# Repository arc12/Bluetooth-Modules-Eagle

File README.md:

# Bluetooth Modules Eagle CAD Files
"Breakout" boards designed for HM10 and HM11 Bluetooth (BT) modules and pin-equivalent clones (etc) based on TI CC2540/2541 SoC.

These are intended to be usable for both breadboard prototyping and as modules for "finished" items (although admittedly in a DIY concept). Unlike breakouts on the open market, it is strictly a 3.3V approach. Both modules have a 5-pin header exposing the "debug" interface pins of the CC254x which can be used for loading new firmware (see notes below) and probably for actual debugging operations with a suitable IDE. The 5-pin header is semi-detached from the rest of the board due to a milled slot so that it can be cut off if not required (but pay attention to making sure the cut copper tracks don't have short-cuts.

As a "finished" item, the concept for the two boards differs:
- For the HM11 based board, the main header is arranged such that the central 6 pins match the pinout of popular USB-Serial boards based on CH340. The intention is that the BT board is plugged into the same header as is used for loading the firmware and is used to provide wireless serial output from a separate MCU and its associated sensors, or to provide serial input for control etc. Notice that there is a cuttable (and re-solderable) link adjacent to the header pins where the CH340 has DTR and RTS/CTS pins. Cut these if these are being used for bootloader control.
- For the HM10 based board, the scenario in mind is that the CC254x is used without a controlling MCU, with its I/O pins being used for various sensors or output connected to the main header.

Each board has one resistor and one capacitor as 1206 size SMD pads. These are optional; the capacitor is good practice for power supply and the resistor is intended for the "finished" scenarios.

## Changing Firmware
This is relevant to "clone" modules, although it may not work on all clones (definitely not if the CC254x is not genuine).

There are two fairly easy approaches:
- Using an ESP8266. See: https://github.com/Jason2866/CCLoader
- Using a Raspberry Pi. See: https://github.com/exotulip/CC2541-programmer

There are a lot of people who have essentially re-hashed the ESP8266 instructions and published online and the arduino forum is full of various accounts of success or failure. Using the boards presented here, with 3.3V native devices such as the RPi and ESP8266 should make life easier.

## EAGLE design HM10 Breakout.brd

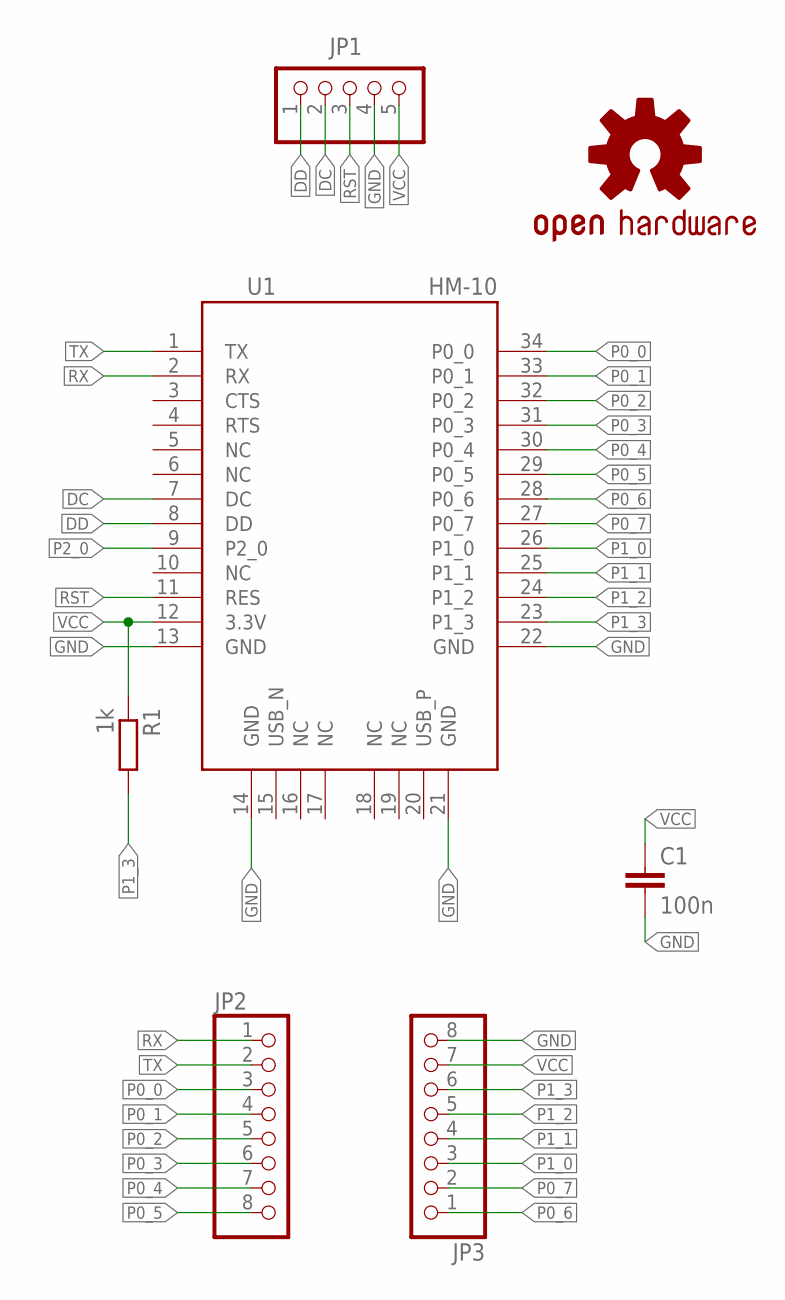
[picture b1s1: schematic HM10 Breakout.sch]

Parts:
C1: 100n; 1206
JP1: PINHD-1X5; 1X05
JP2, JP3: PINHD-1X8; 1X08
LOGO1: OSHW-LOGOM; OSHW-LOGO-M
R1: 1k; R1206
U1: HM-10

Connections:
DC: JP1.2, U1.7 (DC)
DD: JP1.1, U1.8 (DD)
GND: C1.2, JP1.4, JP3.8, U1.13 (GND), U1.14 (GND), U1.21 (GND), U1.22 (GND)
P0_0: JP2.3, U1.34 (P0_0)
P0_1: JP2.4, U1.33 (P0_1)
P0_2: JP2.5, U1.32 (P0_2)
P0_3: JP2.6, U1.31 (P0_3)
P0_4: JP2.7, U1.30 (P0_4)
P0_5: JP2.8, U1.29 (P0_5)
P0_6: JP3.1, U1.28 (P0_6)
P0_7: JP3.2, U1.27 (P0_7)
P1_0: JP3.3, U1.26 (P1_0)
P1_1: JP3.4, U1.25 (P1_1)
P1_2: JP3.5, U1.24 (P1_2)
P1_3: JP3.6, R1.2, U1.23 (P1_3)
P2_0: U1.9 (P2_0)
RST: JP1.3, U1.11 (RES)
RX: JP2.1, U1.2 (RX)
TX: JP2.2, U1.1 (TX)
VCC: C1.1, JP1.5, JP3.7, R1.1, U1.12 (3.3V)

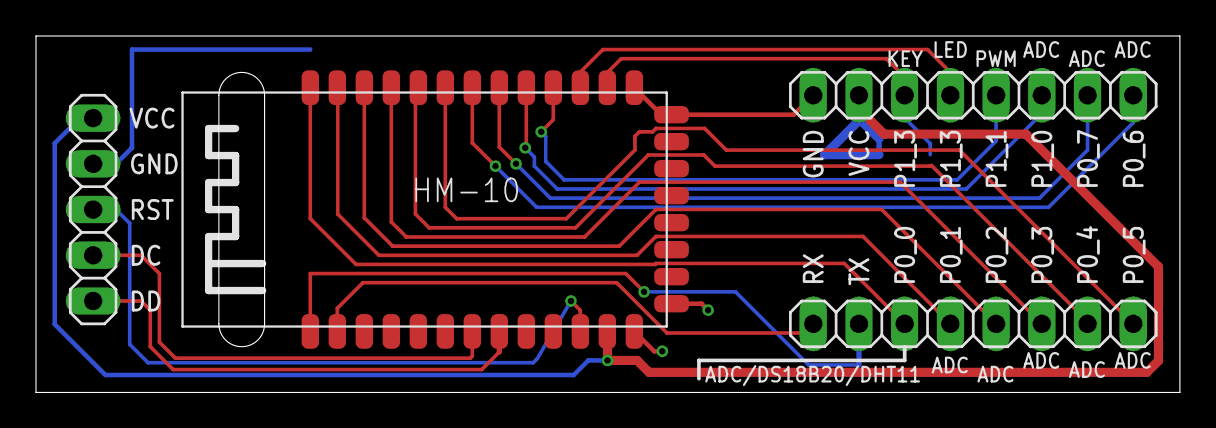
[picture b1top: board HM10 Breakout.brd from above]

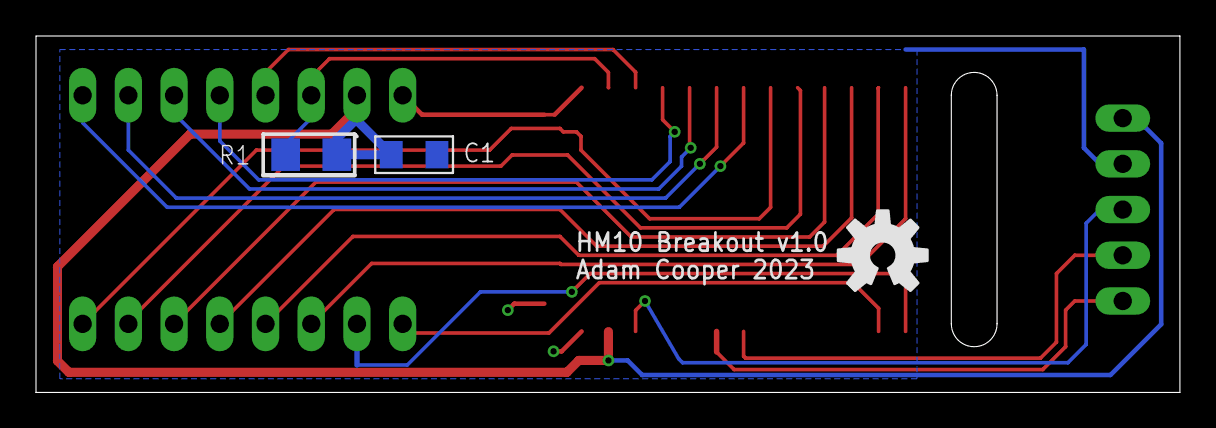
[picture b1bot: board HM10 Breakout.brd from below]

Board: 2 copper layers, 63.6 x 19.8 mm, 7 parts (3 on the bottom side), 19 nets.

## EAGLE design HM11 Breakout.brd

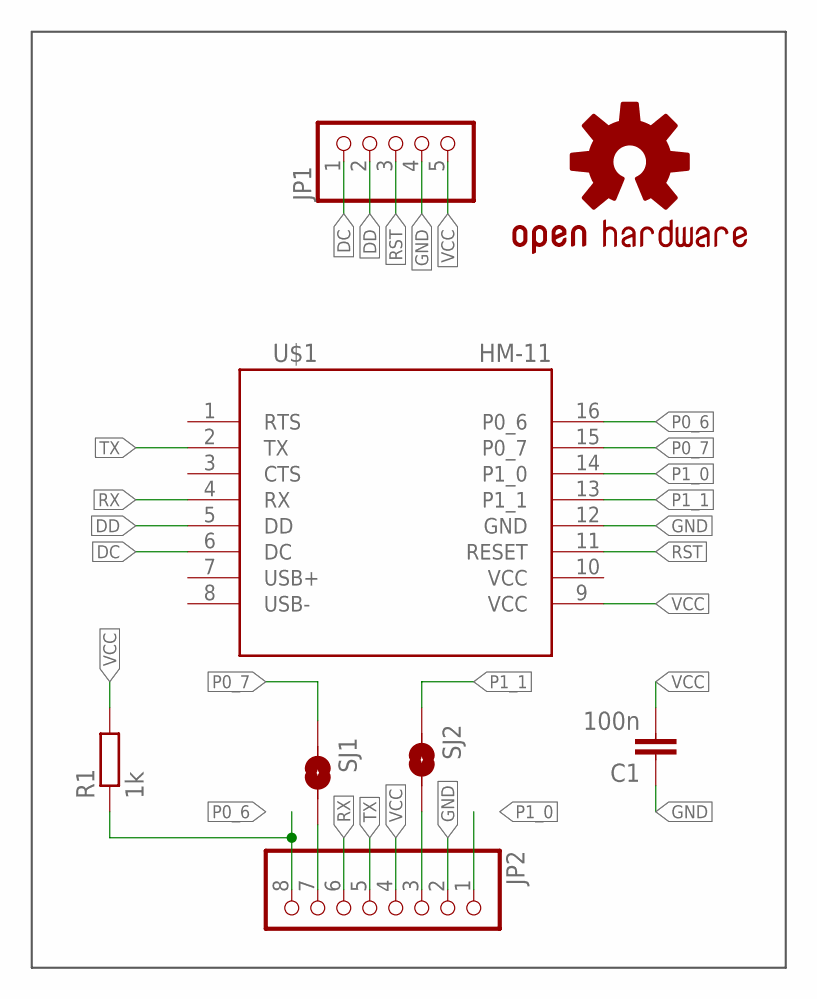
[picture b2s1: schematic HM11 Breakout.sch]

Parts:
C1: 100n; 1206
JP1: PINHD-1X5; 1X05
JP2: PINHD-1X8; 1X08
LOGO1: OSHW-LOGOM; OSHW-LOGO-M
R1: 1k; R1206
SJ1, SJ2: SOLDERJUMPERTRACE; SJ_2S-TRACE
U$1: HM-11

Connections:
DC: JP1.1, U$1.6 (DC)
DD: JP1.2, U$1.5 (DD)
GND: C1.1, JP1.4, JP2.2, U$1.12 (GND)
unnamed: JP2.7, SJ1.1
unnamed: JP2.3, SJ2.1
P0_6: JP2.8, R1.1, U$1.16 (P0_6)
P0_7: SJ1.2, U$1.15 (P0_7)
P1_0: JP2.1, U$1.14 (P1_0)
P1_1: SJ2.2, U$1.13 (P1_1)
RST: JP1.3, U$1.11 (RESET)
RX: JP2.6, U$1.4 (RX)
TX: JP2.5, U$1.2 (TX)
VCC: C1.2, JP1.5, JP2.4, R1.2, U$1.9 (VCC)

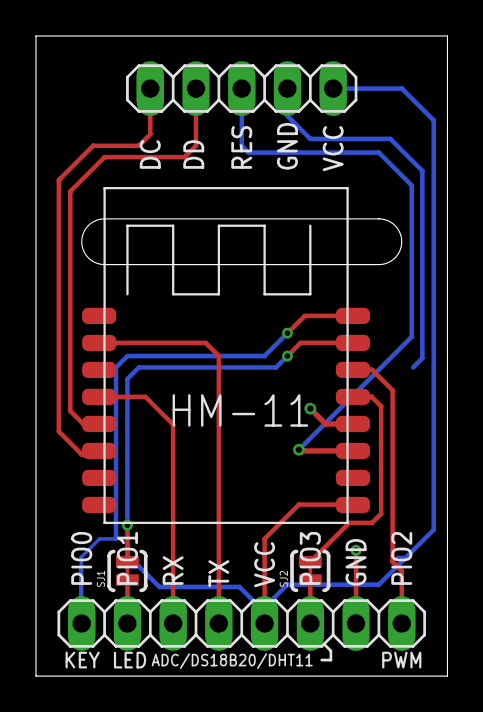
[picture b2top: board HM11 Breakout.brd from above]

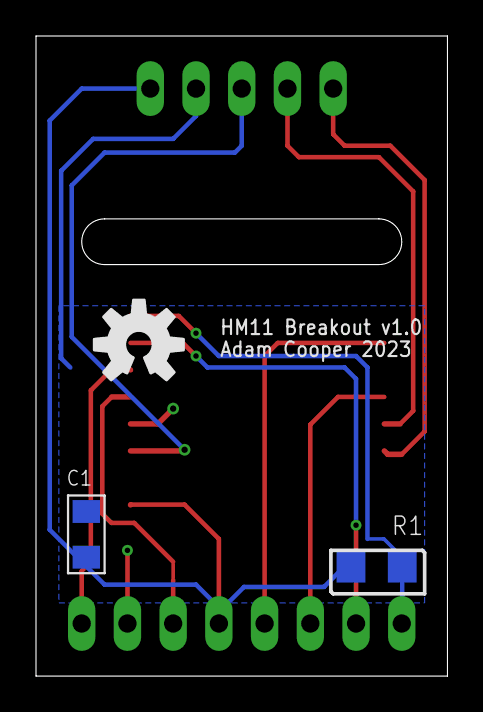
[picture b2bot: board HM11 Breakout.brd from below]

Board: 2 copper layers, 22.9 x 35.6 mm, 8 parts (3 on the bottom side), 13 nets.

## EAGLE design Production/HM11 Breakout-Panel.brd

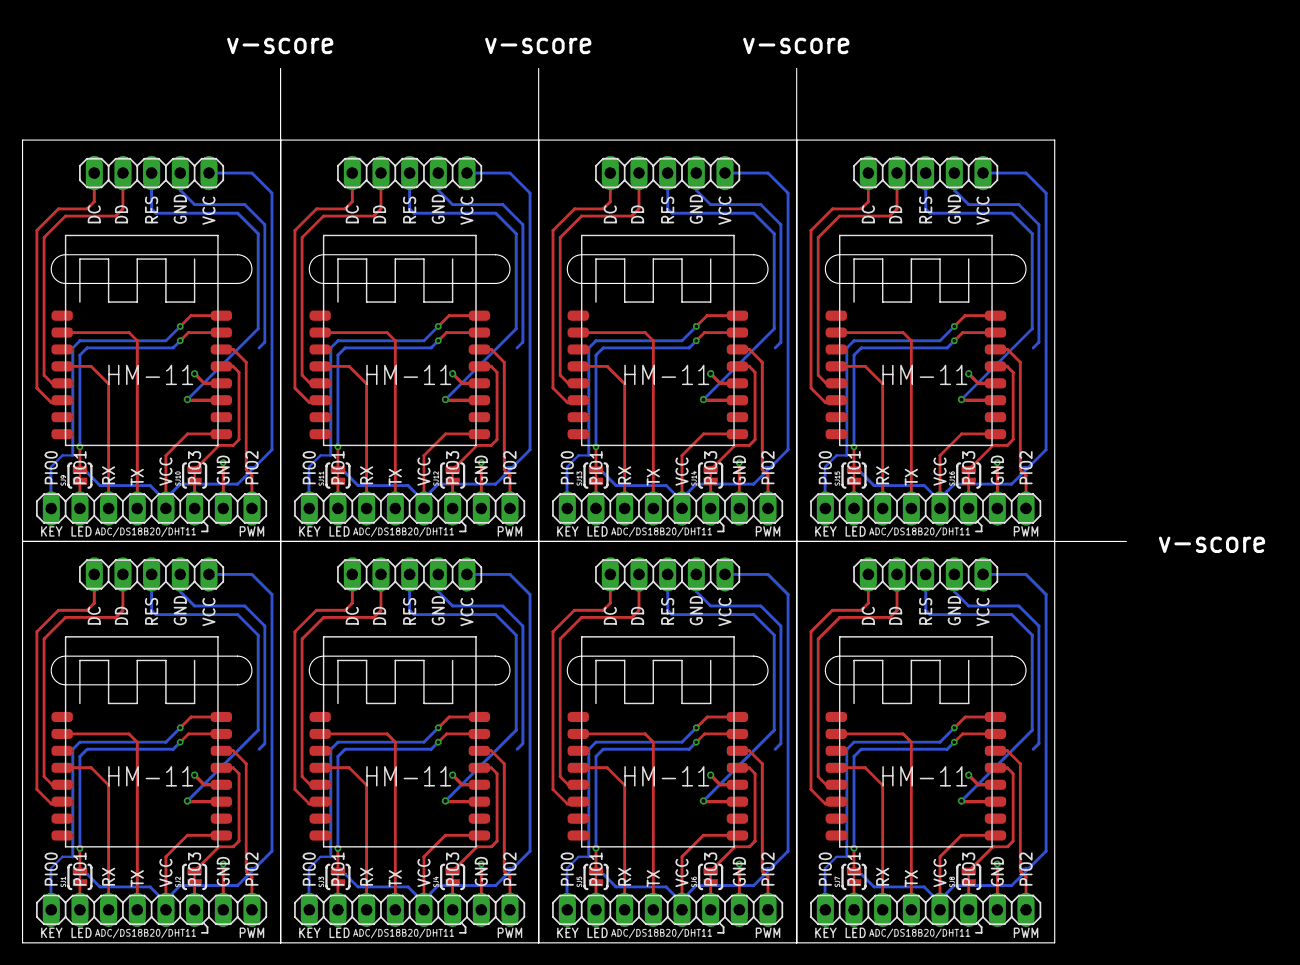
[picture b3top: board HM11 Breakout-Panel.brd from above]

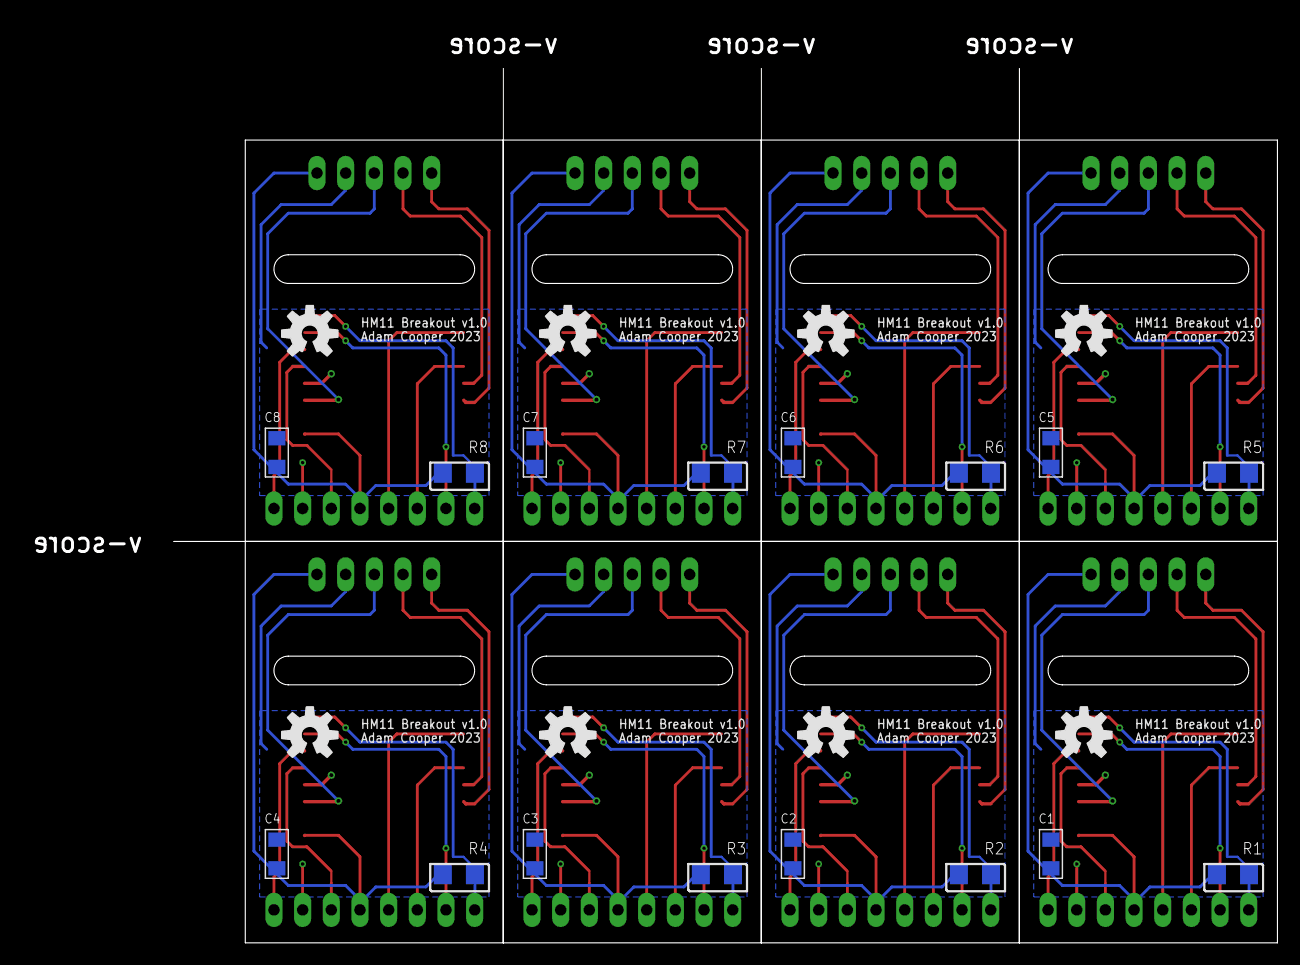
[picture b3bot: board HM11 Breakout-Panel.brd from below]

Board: 2 copper layers, 111.2 x 81.5 mm, 64 parts (24 on the bottom side), 104 nets.

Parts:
C1, C2, C3, C4, C5, C6, C7, C8: 100n; 1206
JP1, JP3, JP5, JP7, JP9, JP11, JP13, JP15: 1X05
JP2, JP4, JP6, JP8, JP10, JP12, JP14, JP16: 1X08
LOGO1, LOGO2, LOGO3, LOGO4, LOGO5, LOGO6, LOGO7, LOGO8: OSHW-LOGOM; OSHW-LOGO-M
R1, R2, R3, R4, R5, R6, R7, R8: 1k; R1206
SJ1, SJ2, SJ3, SJ4, SJ5, SJ6, SJ7, SJ8, SJ9, SJ10, SJ11, SJ12, SJ13, SJ14, SJ15, SJ16: SOLDERJUMPERTRACE; SJ_2S-TRACE
U$1, U$2, U$3, U$4, U$5, U$6, U$7, U$8: HM-11

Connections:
DC: JP1.1, U$1.6
DC1: JP3.1, U$2.6
DC2: JP5.1, U$3.6
DC3: JP7.1, U$4.6
DC4: JP9.1, U$5.6
DC5: JP11.1, U$6.6
DC6: JP13.1, U$7.6
DC7: JP15.1, U$8.6
DD: JP1.2, U$1.5
DD1: JP3.2, U$2.5
DD2: JP5.2, U$3.5
DD3: JP7.2, U$4.5
DD4: JP9.2, U$5.5
DD5: JP11.2, U$6.5
DD6: JP13.2, U$7.5
DD7: JP15.2, U$8.5
GND: C1.1, JP1.4, JP2.2, U$1.12
GND1: C2.1, JP3.4, JP4.2, U$2.12
GND2: C3.1, JP5.4, JP6.2, U$3.12
GND3: C4.1, JP7.4, JP8.2, U$4.12
GND4: C5.1, JP9.4, JP10.2, U$5.12
GND5: C6.1, JP11.4, JP12.2, U$6.12
GND6: C7.1, JP13.4, JP14.2, U$7.12
GND7: C8.1, JP15.4, JP16.2, U$8.12
unnamed: JP2.7, SJ1.1
unnamed: JP4.7, SJ3.1
unnamed: JP4.3, SJ4.1
unnamed: JP6.7, SJ5.1
unnamed: JP6.3, SJ6.1
unnamed: JP2.3, SJ2.1
unnamed: JP8.7, SJ7.1
unnamed: JP8.3, SJ8.1
unnamed: JP10.7, SJ9.1
unnamed: JP10.3, SJ10.1
unnamed: JP12.7, SJ11.1
unnamed: JP12.3, SJ12.1
unnamed: JP14.7, SJ13.1
unnamed: JP14.3, SJ14.1
unnamed: JP16.7, SJ15.1
unnamed: JP16.3, SJ16.1
P0_1: JP4.8, R2.1, U$2.16
P0_2: SJ3.2, U$2.15
P0_3: JP6.8, R3.1, U$3.16
P0_4: SJ5.2, U$3.15
P0_5: JP8.8, R4.1, U$4.16
P0_6: JP2.8, R1.1, U$1.16
P0_7: SJ1.2, U$1.15
P0_8: SJ7.2, U$4.15
P0_9: JP10.8, R5.1, U$5.16
P0_10: SJ9.2, U$5.15
P0_11: JP12.8, R6.1, U$6.16
P0_12: SJ11.2, U$6.15
P0_13: JP14.8, R7.1, U$7.16
P0_14: SJ13.2, U$7.15
P0_15: JP16.8, R8.1, U$8.16
P0_16: SJ15.2, U$8.15
P1_0: JP2.1, U$1.14
P1_1: SJ2.2, U$1.13
P1_2: JP4.1, U$2.14
P1_3: SJ4.2, U$2.13
P1_4: JP6.1, U$3.14
P1_5: SJ6.2, U$3.13
P1_6: JP8.1, U$4.14
P1_7: SJ8.2, U$4.13
P1_8: JP10.1, U$5.14
P1_9: SJ10.2, U$5.13
P1_10: JP12.1, U$6.14
P1_11: SJ12.2, U$6.13
P1_12: JP14.1, U$7.14
P1_13: SJ14.2, U$7.13
P1_14: JP16.1, U$8.14
P1_15: SJ16.2, U$8.13
RST: JP1.3, U$1.11
RST1: JP3.3, U$2.11
RST2: JP5.3, U$3.11
RST3: JP7.3, U$4.11
RST4: JP9.3, U$5.11
RST5: JP11.3, U$6.11
RST6: JP13.3, U$7.11
RST7: JP15.3, U$8.11
RX: JP2.6, U$1.4
RX1: JP4.6, U$2.4
RX2: JP6.6, U$3.4
RX3: JP8.6, U$4.4
RX4: JP10.6, U$5.4
RX5: JP12.6, U$6.4
RX6: JP14.6, U$7.4
RX7: JP16.6, U$8.4
TX: JP2.5, U$1.2
TX1: JP4.5, U$2.2
TX2: JP6.5, U$3.2
TX3: JP8.5, U$4.2
TX4: JP10.5, U$5.2
TX5: JP12.5, U$6.2
TX6: JP14.5, U$7.2
TX7: JP16.5, U$8.2
VCC: C1.2, JP1.5, JP2.4, R1.2, U$1.9
VCC1: C2.2, JP3.5, JP4.4, R2.2, U$2.9
VCC2: C3.2, JP5.5, JP6.4, R3.2, U$3.9
VCC3: C4.2, JP7.5, JP8.4, R4.2, U$4.9
VCC4: C5.2, JP9.5, JP10.4, R5.2, U$5.9
VCC5: C6.2, JP11.5, JP12.4, R6.2, U$6.9
VCC6: C7.2, JP13.5, JP14.4, R7.2, U$7.9
VCC7: C8.2, JP15.5, JP16.4, R8.2, U$8.9

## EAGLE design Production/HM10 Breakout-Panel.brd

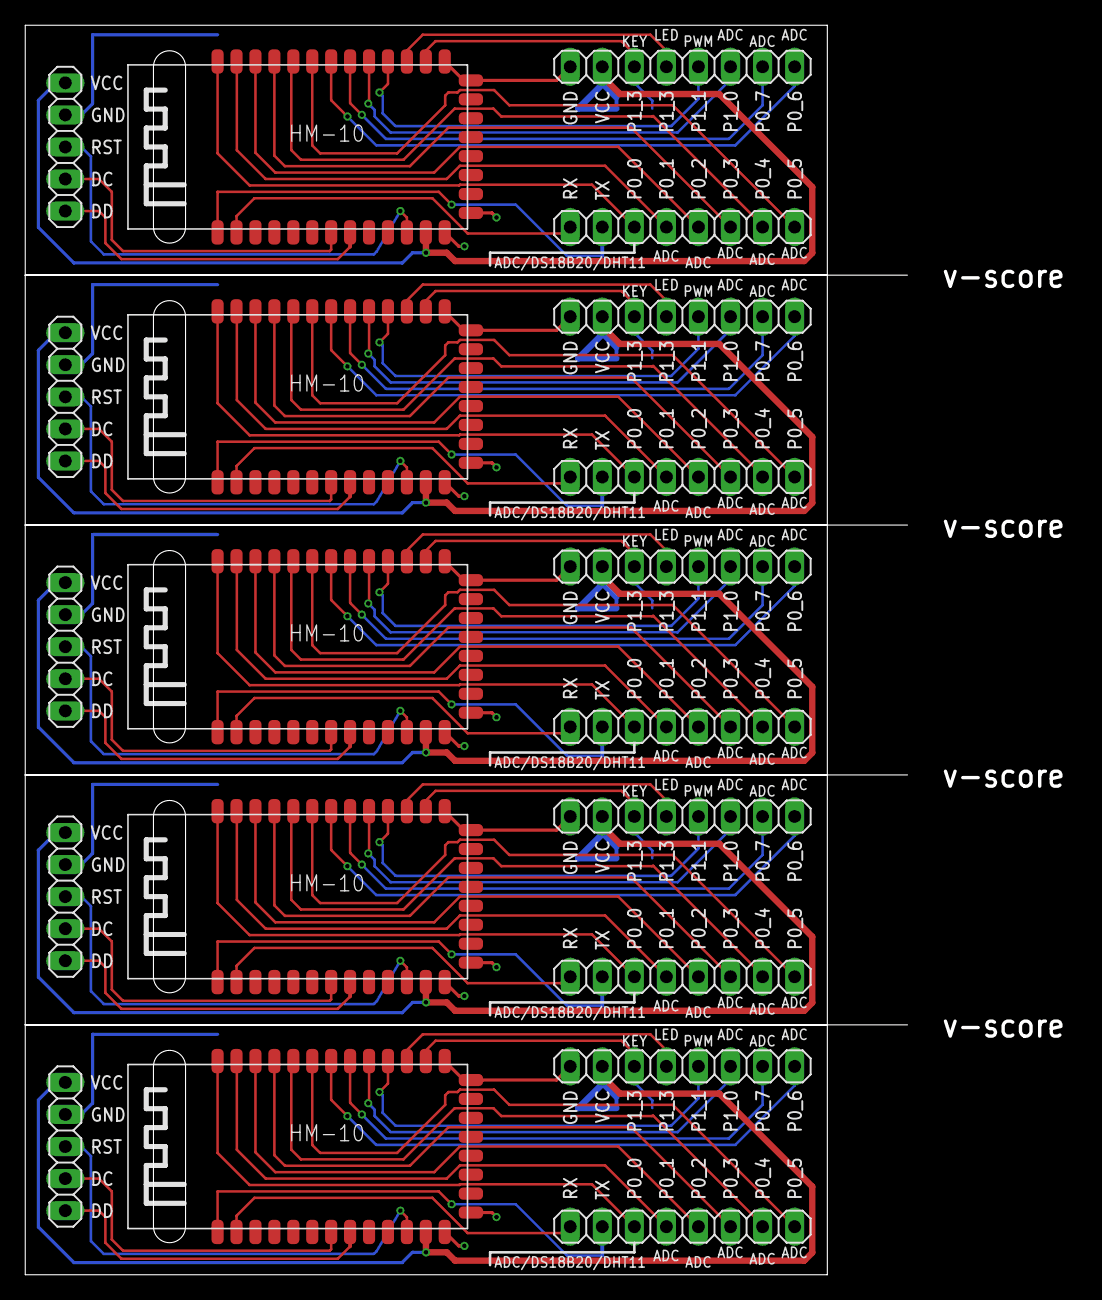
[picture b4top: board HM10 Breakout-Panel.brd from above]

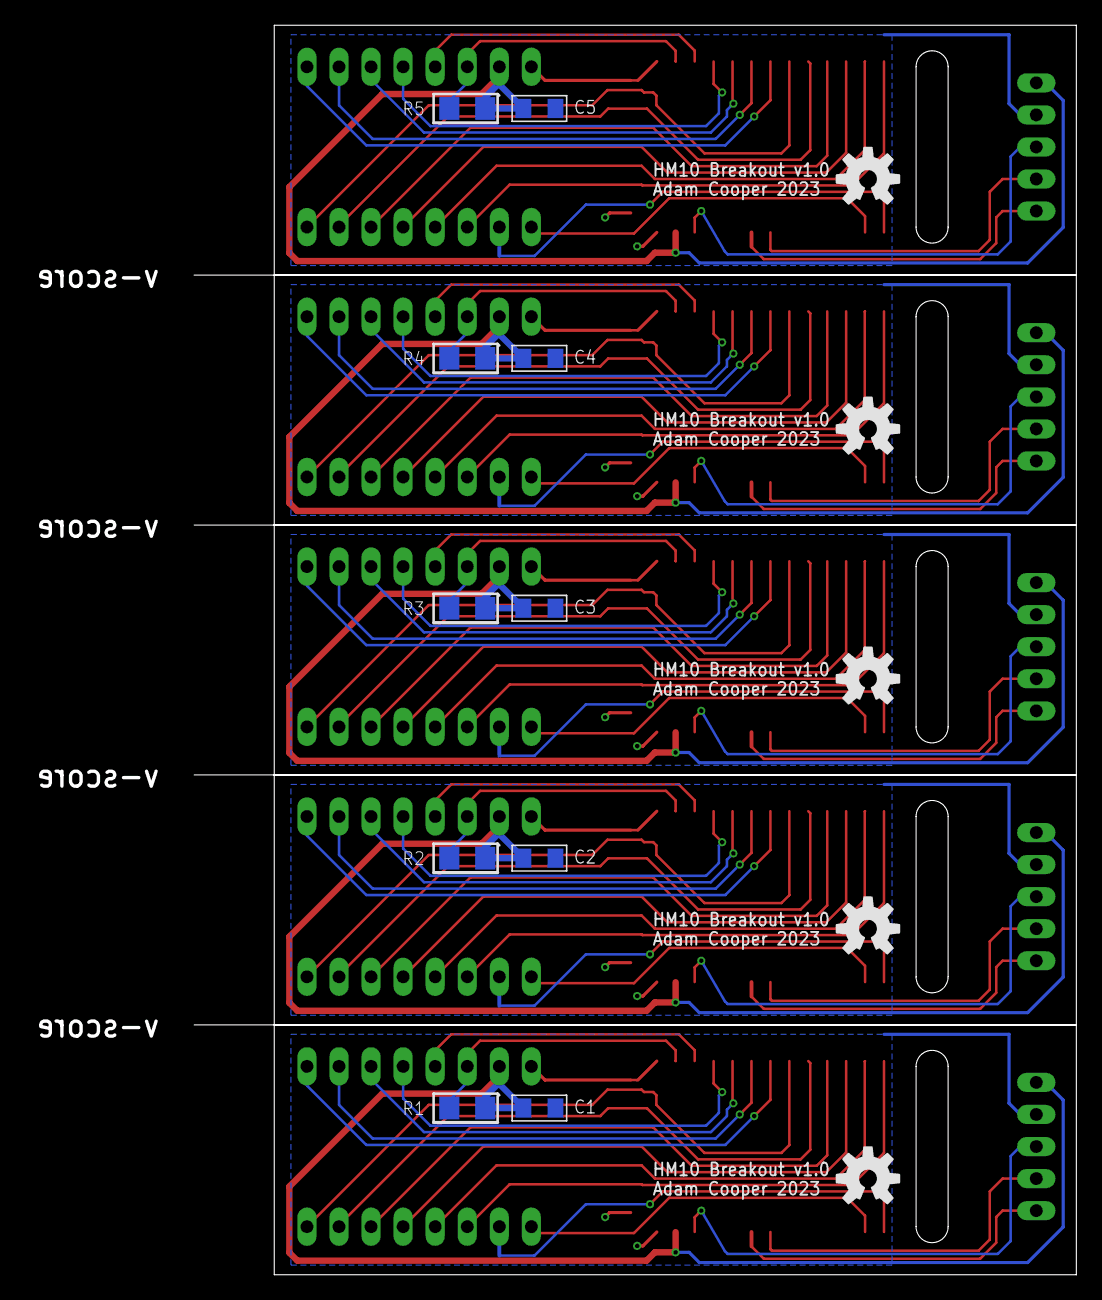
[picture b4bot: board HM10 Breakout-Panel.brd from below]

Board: 2 copper layers, 83.3 x 99.0 mm, 35 parts (15 on the bottom side), 95 nets.

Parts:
C1, C2, C3, C4, C5: 100n; 1206
JP1, JP4, JP7, JP10, JP13: 1X05
JP2, JP3, JP5, JP6, JP8, JP9, JP11, JP12, JP14, JP15: 1X08
LOGO1, LOGO2, LOGO3, LOGO4, LOGO5: OSHW-LOGOM; OSHW-LOGO-M
R1, R2, R3, R4, R5: 1k; R1206
U1, U2, U3, U4, U5: HM-10

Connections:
DC: JP1.2, U1.7
DC1: JP4.2, U2.7
DC2: JP7.2, U3.7
DC3: JP10.2, U4.7
DC4: JP13.2, U5.7
DD: JP1.1, U1.8
DD1: JP4.1, U2.8
DD2: JP7.1, U3.8
DD3: JP10.1, U4.8
DD4: JP13.1, U5.8
GND: C1.2, JP1.4, JP3.8, U1.13, U1.14, U1.21, U1.22
GND1: C2.2, JP4.4, JP6.8, U2.13, U2.14, U2.21, U2.22
GND2: C3.2, JP7.4, JP9.8, U3.13, U3.14, U3.21, U3.22
GND3: C4.2, JP10.4, JP12.8, U4.13, U4.14, U4.21, U4.22
GND4: C5.2, JP13.4, JP15.8, U5.13, U5.14, U5.21, U5.22
P0_0: JP2.3, U1.34
P0_1: JP2.4, U1.33
P0_2: JP2.5, U1.32
P0_3: JP2.6, U1.31
P0_4: JP2.7, U1.30
P0_5: JP2.8, U1.29
P0_6: JP3.1, U1.28
P0_7: JP3.2, U1.27
P0_8: JP5.3, U2.34
P0_9: JP5.4, U2.33
P0_10: JP5.5, U2.32
P0_11: JP5.6, U2.31
P0_12: JP5.7, U2.30
P0_13: JP5.8, U2.29
P0_14: JP6.1, U2.28
P0_15: JP6.2, U2.27
P0_16: JP8.3, U3.34
P0_17: JP8.4, U3.33
P0_18: JP8.5, U3.32
P0_19: JP8.6, U3.31
P0_20: JP8.7, U3.30
P0_21: JP8.8, U3.29
P0_22: JP9.1, U3.28
P0_23: JP9.2, U3.27
P0_24: JP11.3, U4.34
P0_25: JP11.4, U4.33
P0_26: JP11.5, U4.32
P0_27: JP11.6, U4.31
P0_28: JP11.7, U4.30
P0_29: JP11.8, U4.29
P0_30: JP12.1, U4.28
P0_31: JP12.2, U4.27
P0_32: JP14.3, U5.34
P0_33: JP14.4, U5.33
P0_34: JP14.5, U5.32
P0_35: JP14.6, U5.31
P0_36: JP14.7, U5.30
P0_37: JP14.8, U5.29
P0_38: JP15.1, U5.28
P0_39: JP15.2, U5.27
P1_0: JP3.3, U1.26
P1_1: JP3.4, U1.25
P1_2: JP3.5, U1.24
P1_3: JP3.6, R1.2, U1.23
P1_4: JP6.3, U2.26
P1_5: JP6.4, U2.25
P1_6: JP6.5, U2.24
P1_7: JP6.6, R2.2, U2.23
P1_8: JP9.3, U3.26
P1_9: JP9.4, U3.25
P1_10: JP9.5, U3.24
P1_11: JP9.6, R3.2, U3.23
P1_12: JP12.3, U4.26
P1_13: JP12.4, U4.25
P1_14: JP12.5, U4.24
P1_15: JP12.6, R4.2, U4.23
P1_16: JP15.3, U5.26
P1_17: JP15.4, U5.25
P1_18: JP15.5, U5.24
P1_19: JP15.6, R5.2, U5.23
RST: JP1.3, U1.11
RST1: JP4.3, U2.11
RST2: JP7.3, U3.11
RST3: JP10.3, U4.11
RST4: JP13.3, U5.11
RX: JP2.1, U1.2
RX1: JP5.1, U2.2
RX2: JP8.1, U3.2
RX3: JP11.1, U4.2
RX4: JP14.1, U5.2
TX: JP2.2, U1.1
TX1: JP5.2, U2.1
TX2: JP8.2, U3.1
TX3: JP11.2, U4.1
TX4: JP14.2, U5.1
VCC: C1.1, JP1.5, JP3.7, R1.1, U1.12
VCC1: C2.1, JP4.5, JP6.7, R2.1, U2.12
VCC2: C3.1, JP7.5, JP9.7, R3.1, U3.12
VCC3: C4.1, JP10.5, JP12.7, R4.1, U4.12
VCC4: C5.1, JP13.5, JP15.7, R5.1, U5.12

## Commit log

2023-06-08 Initial boards. finished but for superficial stuff
2023-06-08 change licence
2023-06-09 amend gitignore for panelisation output we don't want to keep
2023-06-09 add version & attribution text
2023-06-09 panelised boards
2023-06-09 Add Gerber files for v1.0 as produced for Seeed Studio
2023-06-09 Add ReadMe info on using the boards
